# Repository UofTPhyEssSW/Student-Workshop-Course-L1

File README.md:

# Student-Workshop-Course-L1

<p>
This is a non-credit Introduction to Electronics Graduate course for University of Toronto, Physics Gradute students, held over four, three-hour sessions which consist of one hour of lecture and two hours of practical time.
</p>

## Course Summary

<p>
This course is an Introduction to Electronics course where the student will learn how to solder through hole and surface mount components as well as learn about data acquisition (DAQ), power supplies, digital and analog electronics circuits. During the course the students will build a single channel DAQ board that measures ambient temperature and an Arduino Uno clone, which is theirs to take home. Please note that class has a maximum of 4 students and must have a minimum of 2 students registered for the class to be held.

If the class is full and your are still interested, please add yourself to the waiting list. We will try to schedule another course as soon as possible.
</p>

<a href="https://plrs.physics.utoronto.ca/course-listing/">Available Courses</a>

# Aruduino Framework
<p>
The Arduino IDE 2 is used to demostrate the Phyduino Pico and Analog Front End board. Since these are custom boards a new board manager and libraries must be installed in the IDE for the boards to be programmed. (<a href="https://docs.arduino.cc/software/ide-v2/tutorials/ide-v2-board-manager">instructions here</a>). 
</p>

# Required Arduino Libraries 
- <a href="https://github.com/sparkfun/SparkFun_STUSB4500_Arduino_Library/tree/7f76188b7900d930aeb7908319d463b6446257c6">Sparkfun STUSB4500 Arduino library</a>
- <a href="https://github.com/UofTPhyEssSW/Student-Workshop-Course-L1/tree/main/arduino/libraries/max11635_adc">MAX11635 ADC Arduino Libray</a>
- <a href="https://github.com/UofTPhyEssSW/Student-Workshop-Course-L1/tree/main/arduino/libraries/phyduino_pico">Phyduino Board Library</a>
- <a href="https://github.com/UofTPhyEssSW/Student-Workshop-Course-L1/tree/main/arduino/libraries/Analog_Front_End_Arduino_Library">Analog Front End Arduino Library</a>
- <a href="https://github.com/mathertel/RotaryEncoder">Rotary Encoder Library</a>
# Hardware 

<p>
All circuit boards for this course were designed using <a href="https://www.kicad.org/">KiCad EDA</a> opensource software to make the schematic and PCB design files easy to access for the student. It's not requirement for the student to understand schematic symbols or PCB design the files are there for reference.
</p>

## Boards

- <a href="https://github.com/UofTPhyEssSW/Student-Workshop-Course-L1/tree/main/hardware/phyduino_pico">Phyduino Pico Microcontroller board</a>
- <a href="https://github.com/UofTPhyEssSW/Student-Workshop-Course-L1/tree/main/hardware/analog_front_end_shield">Analog Front End board</a>

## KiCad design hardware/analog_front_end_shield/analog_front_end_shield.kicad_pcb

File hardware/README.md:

# Course Hardware
<p>
There are two boards that are built by the students in the course. The first is the Analog Front End PCB with helps the 
student practise through hole soldering. The second is the Phyduino Pico PCB which continues the soldering training, 
learning how solder surface mount components.
</p>
<p>
Each board is designed using open source software <a href="https://www.kicad.org/">KiCAD EDA</a> design software.
</p>

# Analog Front End PCB

<p>
The Analog Front End (AFE) Board is a demonstration board that is specifically designed to interface with the Phyduino 
Pico board, though it is compatible with other Arduino boards. It is used to train students on good through hole 
soldering techniques, basic data acquisition (DAQ) techniques, and digital interface.
</p>
<p>
The AFE board has a <a href="https://www.ti.com/product/LMT84/part-details/LMT84LPM">LMT84LPM</a> temperature sensor with 
an analog output. Its temperature range is –50°C to 150°C. This sensor is used to demonstrate DAQ circuit design and step 
necessary to acquire data from analog signal. The temperature signal is output on A0 or A3 depending on JP2 jumper position. 
Other than the temperature signals the AFE board also outputs analog signals from the sensor connector (J2), the potentiometer (RV1), 
and the voltage output of the LMT84 (U1) temperature sensor before signal conditioning.
</p>
<p>
In addition to analog signals the AFE board also has digital input and output. The rotary encoder (ENC1) in used for 
digital input which can be used to control parameter within the Phyduino Pico program being run. LED's D1 and D2 can be 
used to output current status of the program or just flash on and off to indicate the program has not froze.
</p>

# Phyduino Pico PCB

<p>
The Phyduino Pico is an Arduino compatible microcontroller board the can be programmed using the <a href="https://docs.arduino.cc/software/ide-v2">Arduino IDE</a>. The Phyduino Pico uses the <a href="https://www.raspberrypi.com/products/rp2040/">Raspberry PI Pico micorcontroller</a> (RP2040) with 2 ARM Cortex-M0+ processors (133MHz) and 264KB of RAM. All programming code is stored in an external 16MB flash chip that can be both programming memory and solid state drive. The microcontroller can be program in C/C++ or <a href="https://www.raspberrypi.com/documentation/microcontrollers/micropython.html">MicroPython</a>. This course only shows examples with C/C++ programming, however there are many tutorials online for programming the RP2040 with MicroPython. 
</p>
<p>
The Phyduino Pico board is power using the USB Power delivery through the USB-C connector. Power delivery is negotiated throught the CC lines on the USB-C connector using the <a href="https://www.st.com/en/interfaces-and-transceivers/stusb4500.html">STUSB4500</a> USB PD controller. The STUSB4500 is programmed to negotiated for 3 power profiles, +5.0V(default), +9.0V, and +20V. The controller will try to negotiate for the high one available. By default all power delivery devices must have at least one profile by default +5.0V. The USB-C connector is used to both power and communicate with the board. Power for the board is regulated through 2, <a href="https://www.ti.com/product/TPS54231?dcmp=dsproject&hqs=td&#doctype2">TPS54231</a> DC/DC converters that steps down the USB VBus voltage to +3.3V and +5.0V.The +3.3V DC/DC regulator is enabled when the USB VBus voltage is above 4.5V. The +5.0V regulator is enabled when USB VBus voltage is above 7.0V. Each power rail on the board the has a led to indicate if the power is active, red for VBus, yellow for +3.3V and green for +5.0V. This allows the user to visual assess which power rails are active. If the the green led is off the USB-PD controller could not negotiate a high power then the default +5.0V. Power is output from the board through J2. +VUSB on J2 is connected directly to the USB VBus if the connected shield board is cannot accommodate the voltage here concider using a linear regulator to being down the voltage required by the shield board. 
</p>
<p>
All connector IO's are compatible with <a href="https://content.arduino.cc/assets/A000066-full-pinout.pdf?_gl=1*1w20zu6*_ga*MjA4MzA3Mzg0OS4xNjc2NDAwMDM1*_ga_NEXN8H46L5*MTY4MzkxNDk5MS4yNC4xLjE2ODM5MTgwODAuMC4wLjA.">Arduino UNO Rev3</a> pin outs. The digital IO pins are +3.3V digital IO tolerant. Do not use shield boards that use IO voltage above +3.3V you will damage the RP2040 IO's. The Analog input pins are broken into 2 groups, internal (A0 - A2) and external (A3 - A5). The internal analog signals are connected to the RP2040 microcontroller's internal 12bit 500KSps ADC. The voltage reference for the RP2040 internal ADC is +3.3V so the <b>maximum measurable voltage is +3.3V</b>. The external signals is connected to the Analog Devices <a href="https://www.analog.com/en/products/max11635.html">MAX11635</a> 12bit 300Ksps ADC. The voltage reference for the MAX11635 is 2.048V so the <b>maximum measurable voltage is +2.048V</b>. Exceed any of this maximum voltage for any analog input group with damage either the RP2040 or MAX11635.
</p>

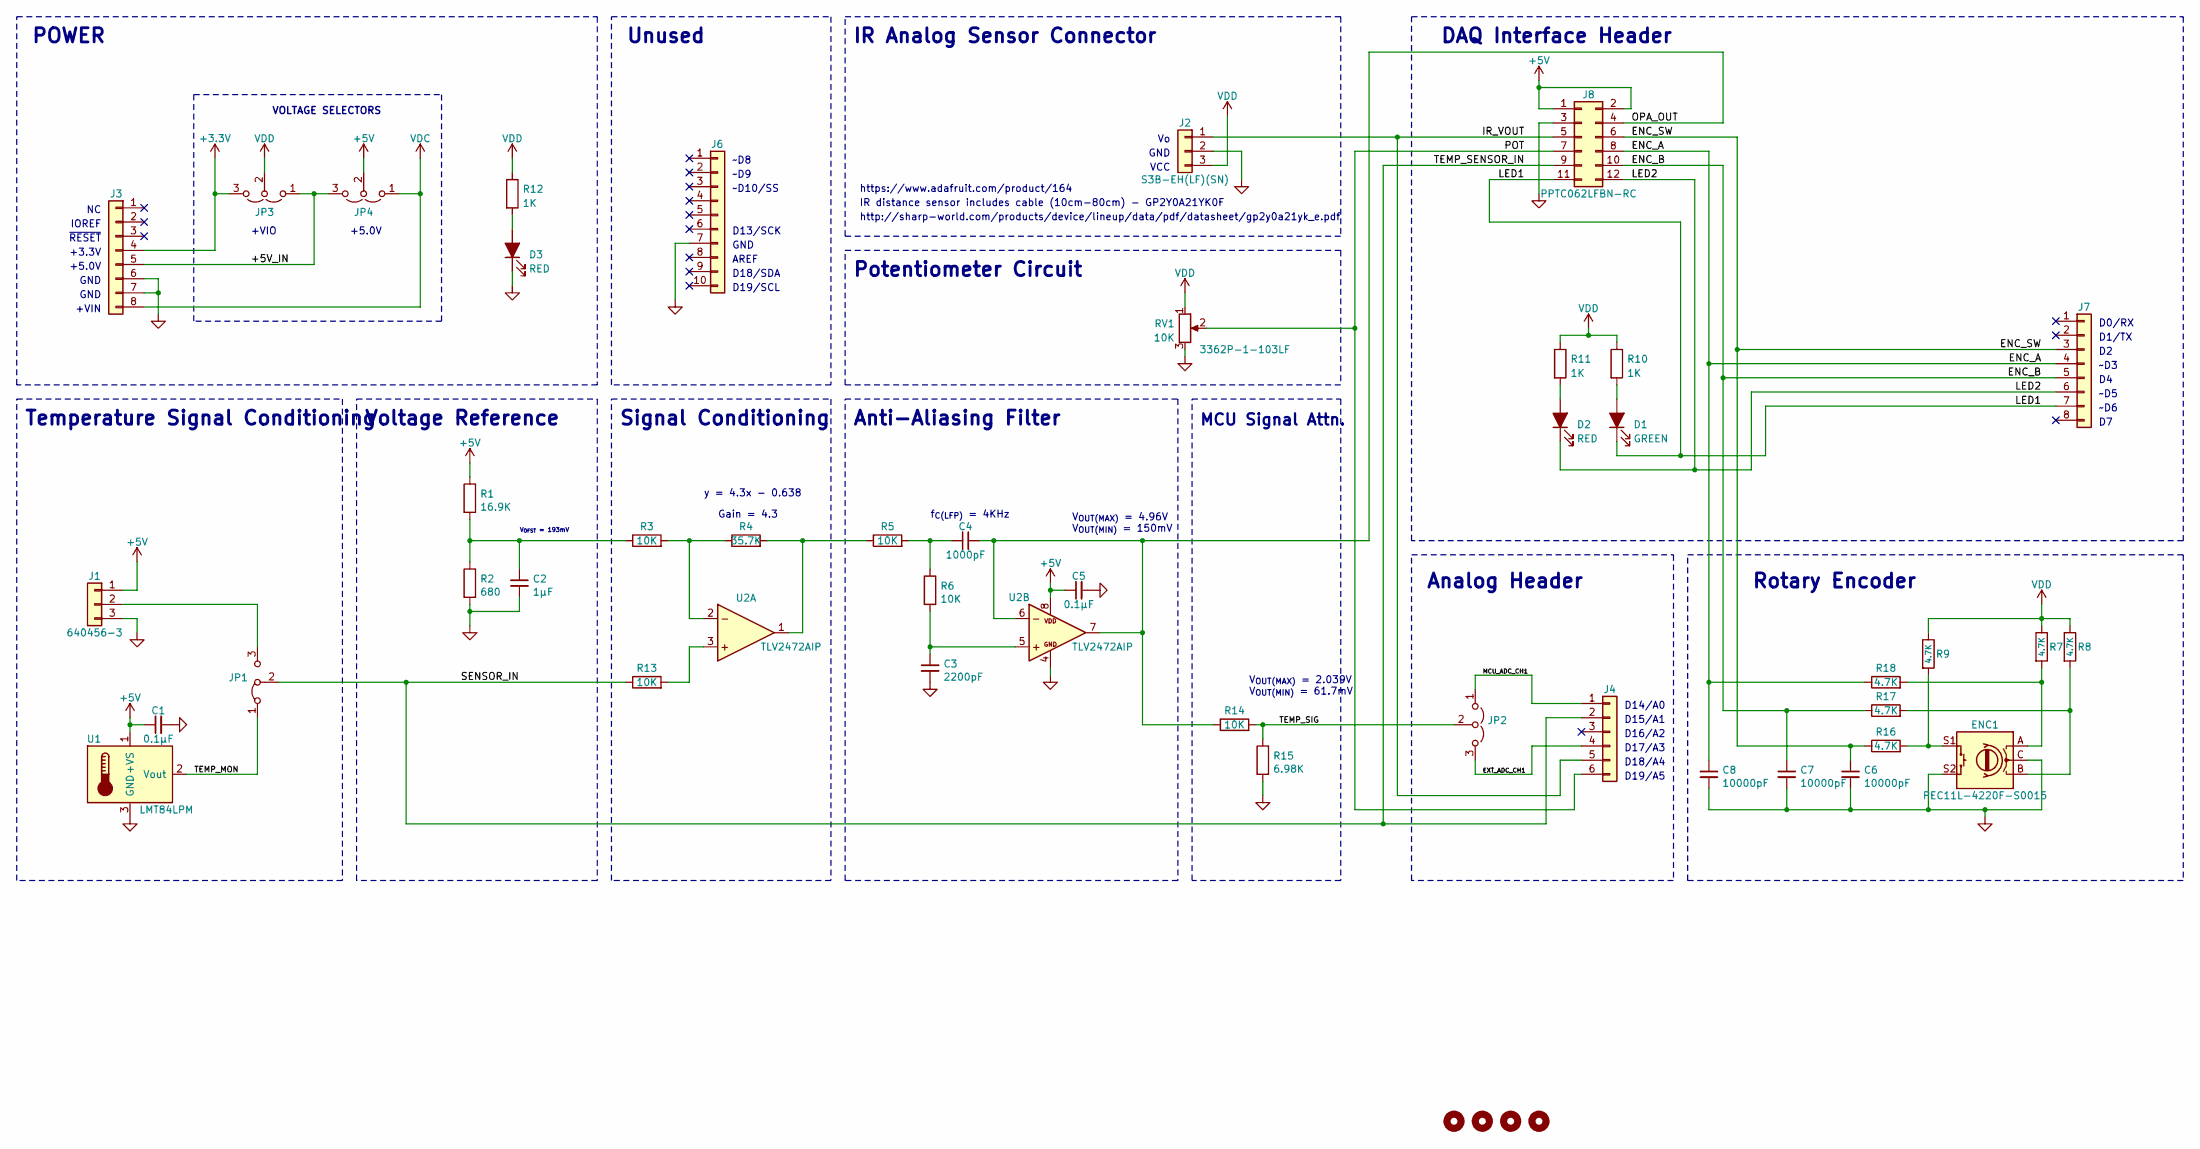
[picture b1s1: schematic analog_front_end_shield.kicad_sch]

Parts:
C1, C5: 0.1µF; C_Disc_D3.8mm_W2.6mm_P2.50mm
C2: 1µF; C_Disc_D3.8mm_W2.6mm_P2.50mm
C3: 2200pF; C_Disc_D3.8mm_W2.6mm_P2.50mm
C4: 1000pF; C_Disc_D3.8mm_W2.6mm_P2.50mm
C6, C7, C8: 10000pF; C_Disc_D3.8mm_W2.6mm_P2.50mm
D1: GREEN; LED_D3.0mm
D2, D3: RED; LED_D3.0mm
ENC1: PEC11L-4220F-S0015; RotaryEncoder_Alps_EC12E-Switch_Vertical_H20mm_CircularMoun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
H1, H2, H3, H4: MountingHole; MountingHole_3.2mm_M3
J1: 640456-3; Molex_KK-254_AE-6410-03A_1x03_P2.54mm_Vertical
J2: S3B-EH(LF)(SN); JST_EH_S3B-EH_1x03_P2.50mm_Horizontal
J3, J7: Conn_01x08; PinHeader_1x08_P2.54mm_Vertical
J4: Conn_01x06; PinHeader_1x06_P2.54mm_Vertical
J6: Conn_01x10; PinHeader_1x10_P2.54mm_Vertical
J8: PPTC062LFBN-RC; PinSocket_2x06_P2.54mm_Vertical
JP1: Jumper_3_Bridged12; PinHeader_1x03_P2.54mm_Vertical
JP2: Jumper_3_Open; PinHeader_1x03_P2.54mm_Vertical
JP3, JP4: Jumper_3_Open; SolderJumper-3_P2.0mm_Open_TrianglePad1.0x1.5mm
R1: 16.9K; R_Axial_DIN0207_L6.3mm_D2.5mm_P10.16mm_Horizontal
R2: 680; R_Axial_DIN0207_L6.3mm_D2.5mm_P10.16mm_Horizontal
R3, R5, R6, R13, R14: 10K; R_Axial_DIN0207_L6.3mm_D2.5mm_P10.16mm_Horizontal
R4: 35.7K; R_Axial_DIN0207_L6.3mm_D2.5mm_P10.16mm_Horizontal
R7, R8, R9, R16, R17, R18: 4.7K; R_Axial_DIN0207_L6.3mm_D2.5mm_P10.16mm_Horizontal
R10, R11, R12: 1K; R_Axial_DIN0207_L6.3mm_D2.5mm_P10.16mm_Horizontal
R15: 6.98K; R_Axial_DIN0207_L6.3mm_D2.5mm_P10.16mm_Horizontal
RV1: 10K; TRIM_3362P-1-103LF
U1: LMT84LPM; TO-92
U2: TLV2472AIP; DIP-8_W7.62mm

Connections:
+3V3: J3.4, JP3.3 (B)
+5V: C1.1, C5.1, J1.1, J8.1, J8.2, JP4.2 (C), R1.1, U1.1 (+VS), U2.8 (V+)
/+5V_IN: J3.5, JP3.1 (A), JP4.3 (B)
/ENC_A: C8.1, J7.4, J8.8, R18.1
/ENC_B: C7.1, J7.5, J8.10, R17.1
/ENC_SW: C6.1, J7.3, J8.6, R16.1
/EXT_ADC_CH1: J4.4, JP2.3 (B)
/IR_VOUT: J2.1, J4.5, J8.5
/LED1: D1.1 (K), J7.7, J8.11
/LED2: D2.1 (K), J7.6, J8.12
/MCU_ADC_CH1: J4.1, JP2.1 (A)
/OPA_OUT: C4.2, J8.4, R14.1, U2.6 (-), U2.7 (OUT)
/POT: J4.6, J8.7, RV1.2
/SENSOR_IN: J4.2, J8.9, JP1.2 (C), R13.1
/TEMP_MON: JP1.1 (A), U1.2 (Vout)
/TEMP_SIG: JP2.2 (C), R14.2, R15.1
GND: C1.2, C2.2, C3.2, C5.2, C6.2, C7.2, C8.2, D3.1 (K), ENC1.C, ENC1.S2, J1.3, J2.2, J3.6, J3.7, J6.7, J8.3, R2.2, R15.2, RV1.3, U1.3 (GND), U2.4 (GND)
unnamed: C2.1, R1.2, R2.1, R3.1
unnamed: C4.1, R5.2, R6.1
unnamed: D1.2 (A), R10.2
unnamed: D2.2 (A), R11.2
unnamed: D3.2 (A), R12.2
unnamed: ENC1.A, R7.2, R18.2
unnamed: ENC1.B, R8.2, R17.2
unnamed: ENC1.S1, R9.2, R16.2
unnamed: J1.2, JP1.3 (B)
unnamed: R13.2, U2.3 (+)
unnamed: R3.2, R4.1, U2.2 (-)
unnamed: R4.2, R5.1, U2.1 (OUT)
unnamed: C3.1, R6.2, U2.5 (+)
VDC: J3.8, JP4.1 (A)
VDD: J2.3, JP3.2 (C), R7.1, R8.1, R9.1, R10.1, R11.1, R12.1, RV1.1

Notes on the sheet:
Signal Conditioning
~D8
AREF
DAQ Interface Header
Anti-Aliasing Filter
D13/SCK
IOREF
VOLTAGE SELECTORS
V_{OUT(MAX)} = 2.039V V_{OUT(MIN)} = 61.7mV
D14/A0
Voltage Reference
~D10/SS
~D9
D17/A3
+5.0V
https://www.adafruit.com/product/164
GND
D19/A5
~D5
D19/SCL
V_{OFST} = 193mV
Unused
~{RESET}
D18/A4
~D6
http://sharp-world.com/products/device/lineup/data/pdf/datasheet/gp2y0a21yk_e.pdf
D16/A2
Temperature Signal Conditioning
f_{C(LFP)} = 4KHz
D1/TX
+VIN
IR Analog Sensor Connector
D18/SDA
~D3
Rotary Encoder
VCC
MCU Signal Attn.
POWER
IR distance sensor includes cable (10cm-80cm) - GP2Y0A21YK0F
D0/RX

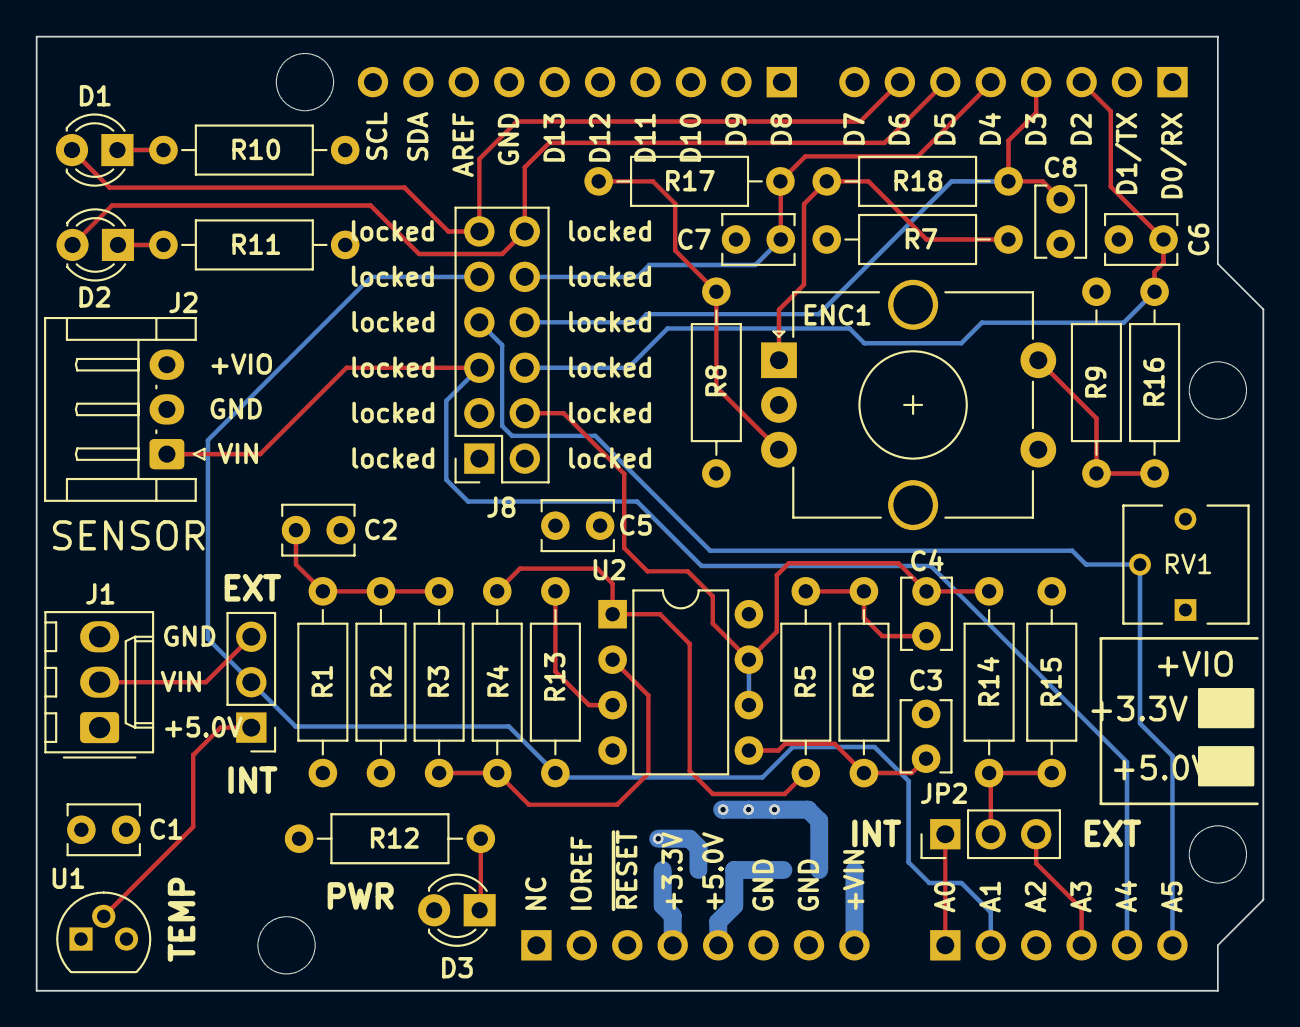
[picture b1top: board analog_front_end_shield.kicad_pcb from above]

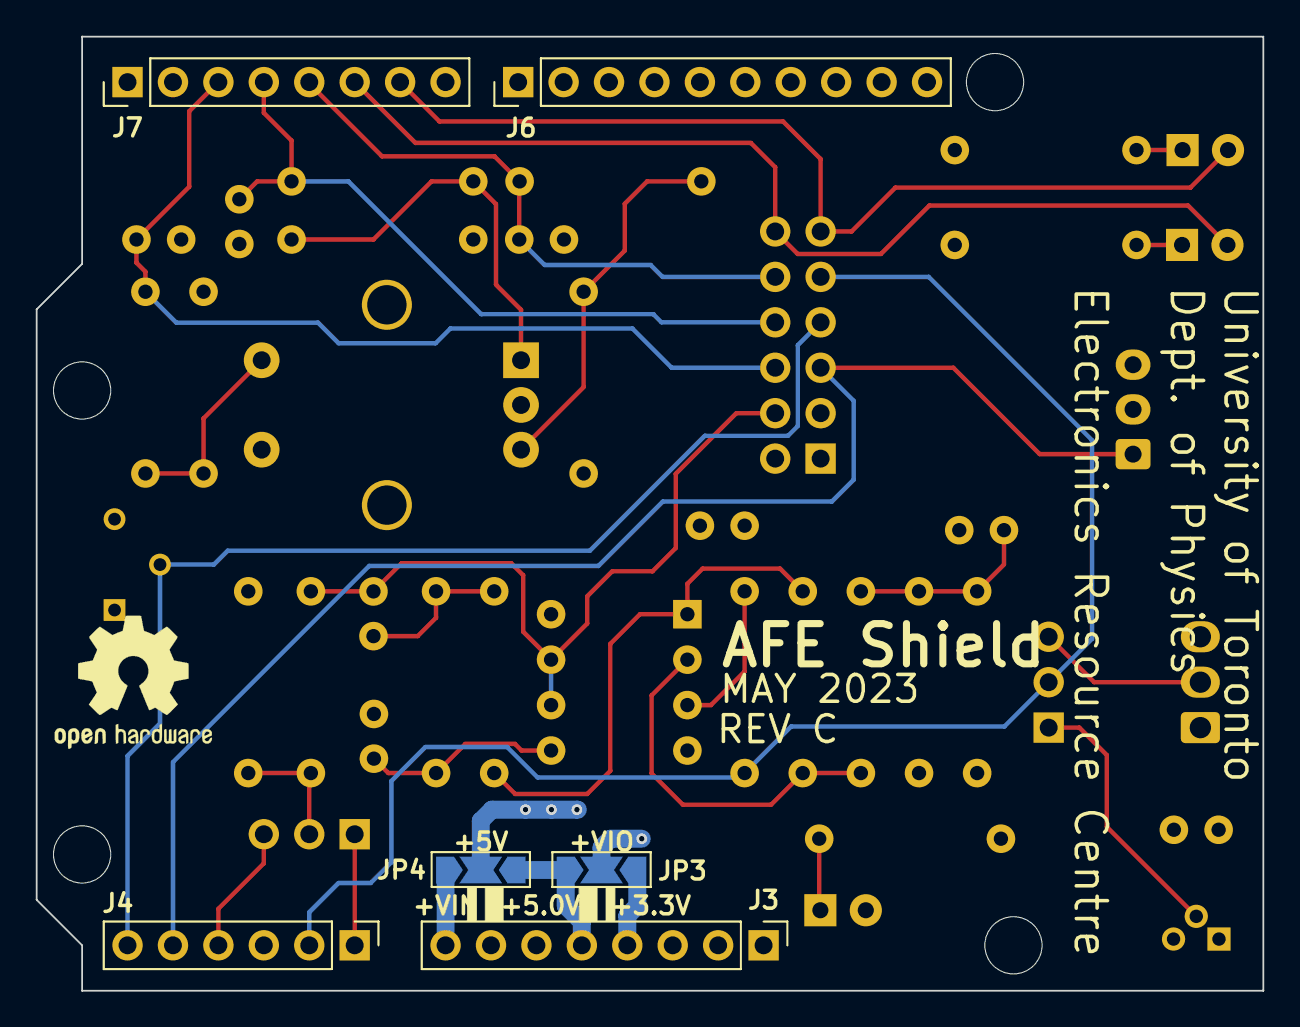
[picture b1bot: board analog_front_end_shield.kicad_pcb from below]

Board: 4 copper layers, 68.6 x 53.3 mm, 48 parts (6 on the bottom side), 32 nets.

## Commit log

2023-03-30 Initial commit, hardware and arduino
    Initial commit of hardware design files, Arduino libraries and board manger repositories.
2023-03-30 Update .gitmodules
    updated .gitmodule format
2023-03-30 Add Sparkfun STUSB4500 library
2023-03-30 Add submodules
    Changed the file directory for the arduino folder and added IDE board manager for RP2040
2023-03-30 update MAX11635 library properties file.
2023-03-30 Update max11635.h
    testing arduino library, making changes to errors.
2023-05-08 Hardware projects added
    Final boards added to repository : Phyduino Pico Rev C and Analog Front End Rev C. includes symbol and front print libraries for each project.
2023-05-09 Add Arduino libraries for Phyduino Pico
2023-05-09 Fixed bugs and tested MAX11635 ADC Arduino Library
    Fixed bugs in library and tested. Ready for publishing.
2023-05-10 MAX11635 IO assignment fix
    Fixed nCNVT and nEOC IO assignments.
2023-05-10 Phyduino library bug fixes and formatting
    Fixed external ADC initialization issue. Removed analog front end example; moving it to another library.
2023-05-10 README doc updates
    first draft of README files.
2023-05-12 Added Analog Front End library
    Initial commit for the AFE shield Arduino library
2023-05-12 Part Number update
    Updated part numbers
2023-05-12 Update main Read Me
    Added Analog Front End library to library list
2023-05-12 README.md update to project
2023-05-12 Updated README links
2023-05-12 Library README updates
2023-05-12 Initial READ ME file for hardware directory
2023-05-12 READ ME updates
2023-05-12 Initial commit for MAX11635 library README
2023-05-12 Update hardware folder README
2023-05-12 Rename MAX11635 folder to correct file structure error on github
2023-05-12 AFE board version correction
2023-05-12 Added submodule Rotary Encoder Library
2023-05-12 Add submodule RotaryEncoder library
2023-05-12 Added README file to libraries folder
2023-05-12 Update README.md
    broken link fixes
2023-05-15 Add .ZIP Library files for non-registered Arduino Libraries
    update .gitignore as well.
2023-05-19 Updated AFE iBoM files
2023-05-19 Update resistor values for amplifier circuit.
2023-05-20 Added board pictures
2023-05-20 Updated images for README
2023-05-21 Add automatic library python script
    added python script to automatically update/create Arduino IDE libraries need for the course.
2023-05-21 Update keyword file for AFE shield library
2023-05-21 Updated pictures in README files
2023-05-21 Updated grammar in README files
2023-05-21 complier error fixes
2023-10-04 MAX11635 ADC library code update and added example
2023-10-04 python help script update
2024-02-01 Phyduino PICO KiCAD project updated, REV D
2024-02-01 Analog Front End library update
2024-02-01 MAX11635 ADC library update
2024-02-01 Phyduino Pico library update
